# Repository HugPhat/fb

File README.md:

this robot has two main parts. The main file belongs to robot's operator and last for remote control
- be careful & good luck-

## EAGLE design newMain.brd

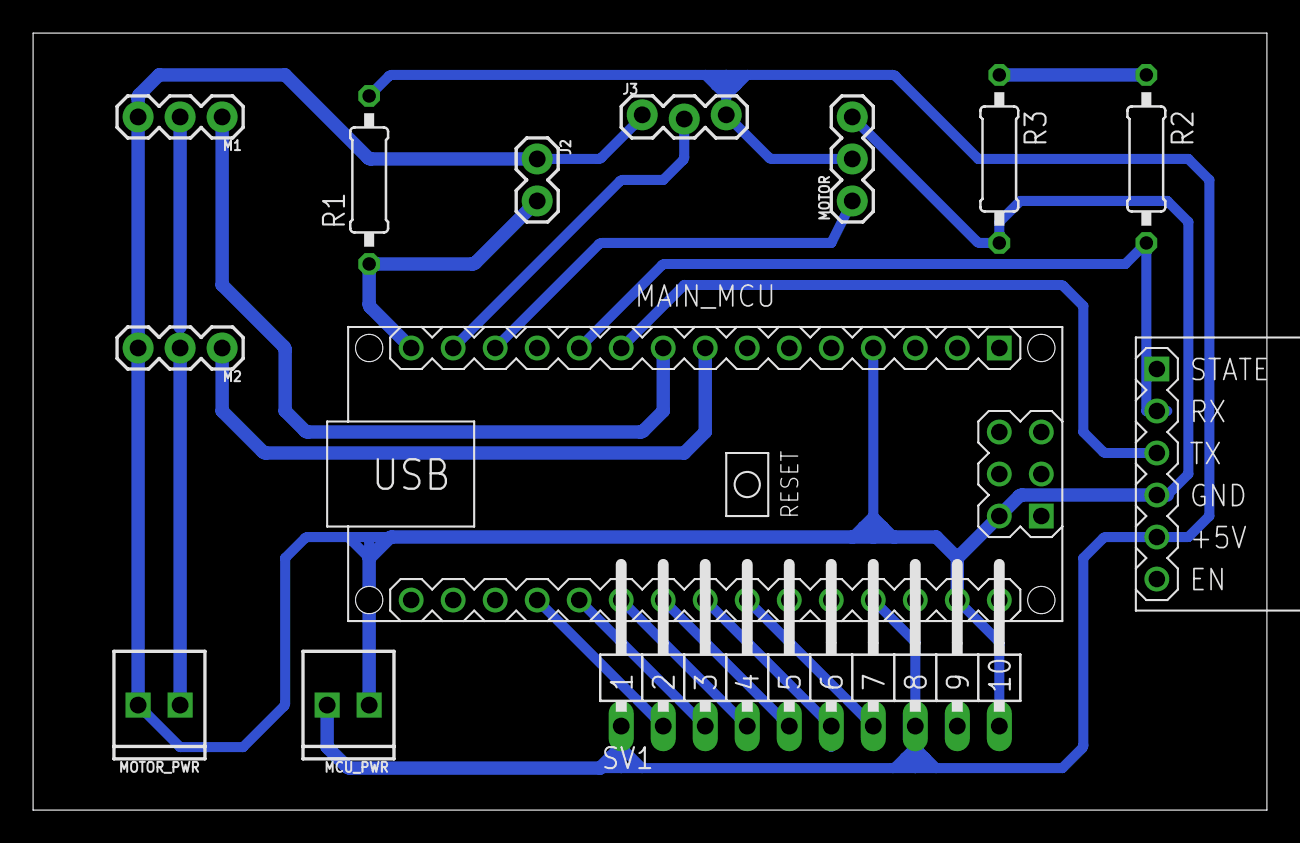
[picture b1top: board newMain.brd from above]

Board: 2 copper layers, 74.6 x 47.0 mm, 13 parts (0 on the bottom side), 17 nets.

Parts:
J2: 1X02
J3: 1X03_LOCK
M1, M2: SERVO; 1X03
MAIN_MCU: ARDUINO-NANO-3.0#ISP
MCU_PWR: 1X02_2.54_SCREWTERM
MOTOR: 455-1750-1-ND; 1X03
MOTOR_PWR: 1X02_2.54_SCREWTERM
R1, R2: 1k; 0207/10
R3: 2k; 0207/10
SV1: MA10-1W
U$1: WIRELESS-BLUETOOTH-HC-05

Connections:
B0: MAIN_MCU.J2.12, SV1.2
B1: MAIN_MCU.J2.11, SV1.3
B2: MAIN_MCU.J2.10, SV1.4
B3: MAIN_MCU.J2.9, SV1.5
B4: MAIN_MCU.J2.8, SV1.6
B5: MAIN_MCU.J2.7, SV1.7
GND: J2.1, J3.1, M1.3, M2.3, MAIN_MCU.J1.4, MAIN_MCU.J2.2, MCU_PWR.P2, MOTOR.3, MOTOR_PWR.P1, R3.2, SV1.10, U$1.4
MAGNET: J2.2, MAIN_MCU.J1.15, R1.1
MOTOR: MAIN_MCU.J1.13, MOTOR.1
unnamed: R2.1, R3.1, U$1.2
OPT: J3.2, MAIN_MCU.J1.14
RX_BLE: MAIN_MCU.J1.11, R2.2
SEV_1: M2.1, MAIN_MCU.J1.8
SEV_2: M1.1, MAIN_MCU.J1.9
TX_BLE: MAIN_MCU.J1.10, U$1.3
VCC_1: M1.2, M2.2, MOTOR_PWR.P2
VCC_2: J3.3, MAIN_MCU.J2.4, MCU_PWR.P1, MOTOR.2, R1.2, SV1.1, U$1.5

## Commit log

2019-05-22 Code
2019-05-22 pcb main

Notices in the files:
parts and their libraries:
SparkFun-Connectors: Licensing: Creative Commons ShareAlike 4.0 International - https://creativecommons.org/licenses/by-sa/4.0
diy-modules: Released under the Creative Commons Attribution 4.0 International License: http://creativecommons.org/licenses/by/4.0
